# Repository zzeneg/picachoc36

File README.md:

# PicaChoc36

Low-profile split keyboard with 36 keys using XIAO controllers.

_Pica pica - european (common) magpie_

## Features

- reversible PCB
- 36 soldered ChocV1 keys
- wired/wireless versions
- top pinky key moved to side
- 3D printed case

### Wired version

- XIAO RP 2040 controller
- QMK firmware
- TRRS or USB-C connection between halves
- rotary encoder on one side
- one status LED

### Wireless version

- XIAO BLE controller
- _[TODO]_ ZMK firmware
- rotary encoder on both sides (ZMK supports only main side for now)
- on/off toggle
- battery connectors

## Photos

wired version with 3d printed case

build process

battery compartment

## Firmware

- QMK - [my fork](https://github.com/zzeneg/qmk_firmware/tree/feature/zzeneg/keyboards/picachoc36), [compiled file](https://github.com/zzeneg/qmk_firmware/releases/download/zzeneg/picachoc36_default.uf2)
- Vial - [my fork](https://github.com/zzeneg/vial-qmk/tree/feature/zzeneg/keyboards/picachoc36), [compiled file](https://github.com/zzeneg/vial-qmk/releases/download/zzeneg/picachoc36_vial.uf2)
- _[TODO]_ ZMK

## Gerber files

- [PCB](./pcb/production/pcb.zip)

## Case files (STL - 3d printed)

Updated wired cases render:

- Wired - [Left](./stl/Plate_case%20v2_left-wired.stl), [left without encoder hole](./stl/Plate_case%20v2_left-wired-no-enc.stl), [right](./stl/Plate_case%20v2_right-wired.stl), [right without encoder hole](./stl/Plate_case%20v2_right-wired-no-enc.stl)
- Wireless - with battery compartment and encoder holes - [left](./stl/Plate-wireless-left.stl), [right](./stl/Plate-wireless-right.stl)
- _[Experimental]_ [Knob](./stl/Knob.stl) for low profile rotary encoder

## Bill of materials

- PCBs
- 3D printed case
- 2 XIAO MCUs - [RP2040](https://www.seeedstudio.com/XIAO-RP2040-v1-0-p-5026.html) for wired version, [nRF52840](https://www.seeedstudio.com/Seeed-XIAO-BLE-nRF52840-p-5201.html) for wireless
- 36 Choc V1 switches
- 36 SMD SOD-123 1N4148 diodes
- 1 or 2 EC11/12 rotary encoder with knob, [low profile](https://keycapsss.com/keyboard-parts/parts/220/alps-alpine-encoder-low-profile-ec12e1220301) is recommended
- _[Wired only]_ [2x USB-C 16pin connector](https://www.aliexpress.com/item/1005003670899595.html) and TRRS jack
- _[Wired only]_ USB-C or TRRS cable
- _[Wireless only]_ 2x Li-Ion 3.7V battery (battery compartment suited for 5×12×21 size)
- _[Wireless only]_ [2x on/off toggle MSK-12C02](https://www.aliexpress.com/item/4000685483225.html)

## Build log

**TODO**

Similar to all other keyboards. Main points:

- solder diodes on **top** side
- solder jumpers - choose wired or wireless on both sides
- for wired version only - solder "no enc" jumper on the side that **does not** have encoder
- for wireless version only - solder on/off switch on **top** side
- if you want USB-C connection, I recommend to solder both TRRS and USB-C to have a backup option, better safe than sorry. Check USB-C pins with multimeter for shorts/continuity, test that encoder works (it uses connection between splits)

⚠️ It's not possible to disassemble the keyboard after soldering switches, so **before** that:

- flash your MCUs with a firmware that supports bootmagic/QK_BOOT/&reset functions
- triple check all keys with tweezers

## Development

For proper KiCad setup install my [zzkeeb](https://github.com/zzeneg/zzkeeb/blob/main/README.md#installation) library.

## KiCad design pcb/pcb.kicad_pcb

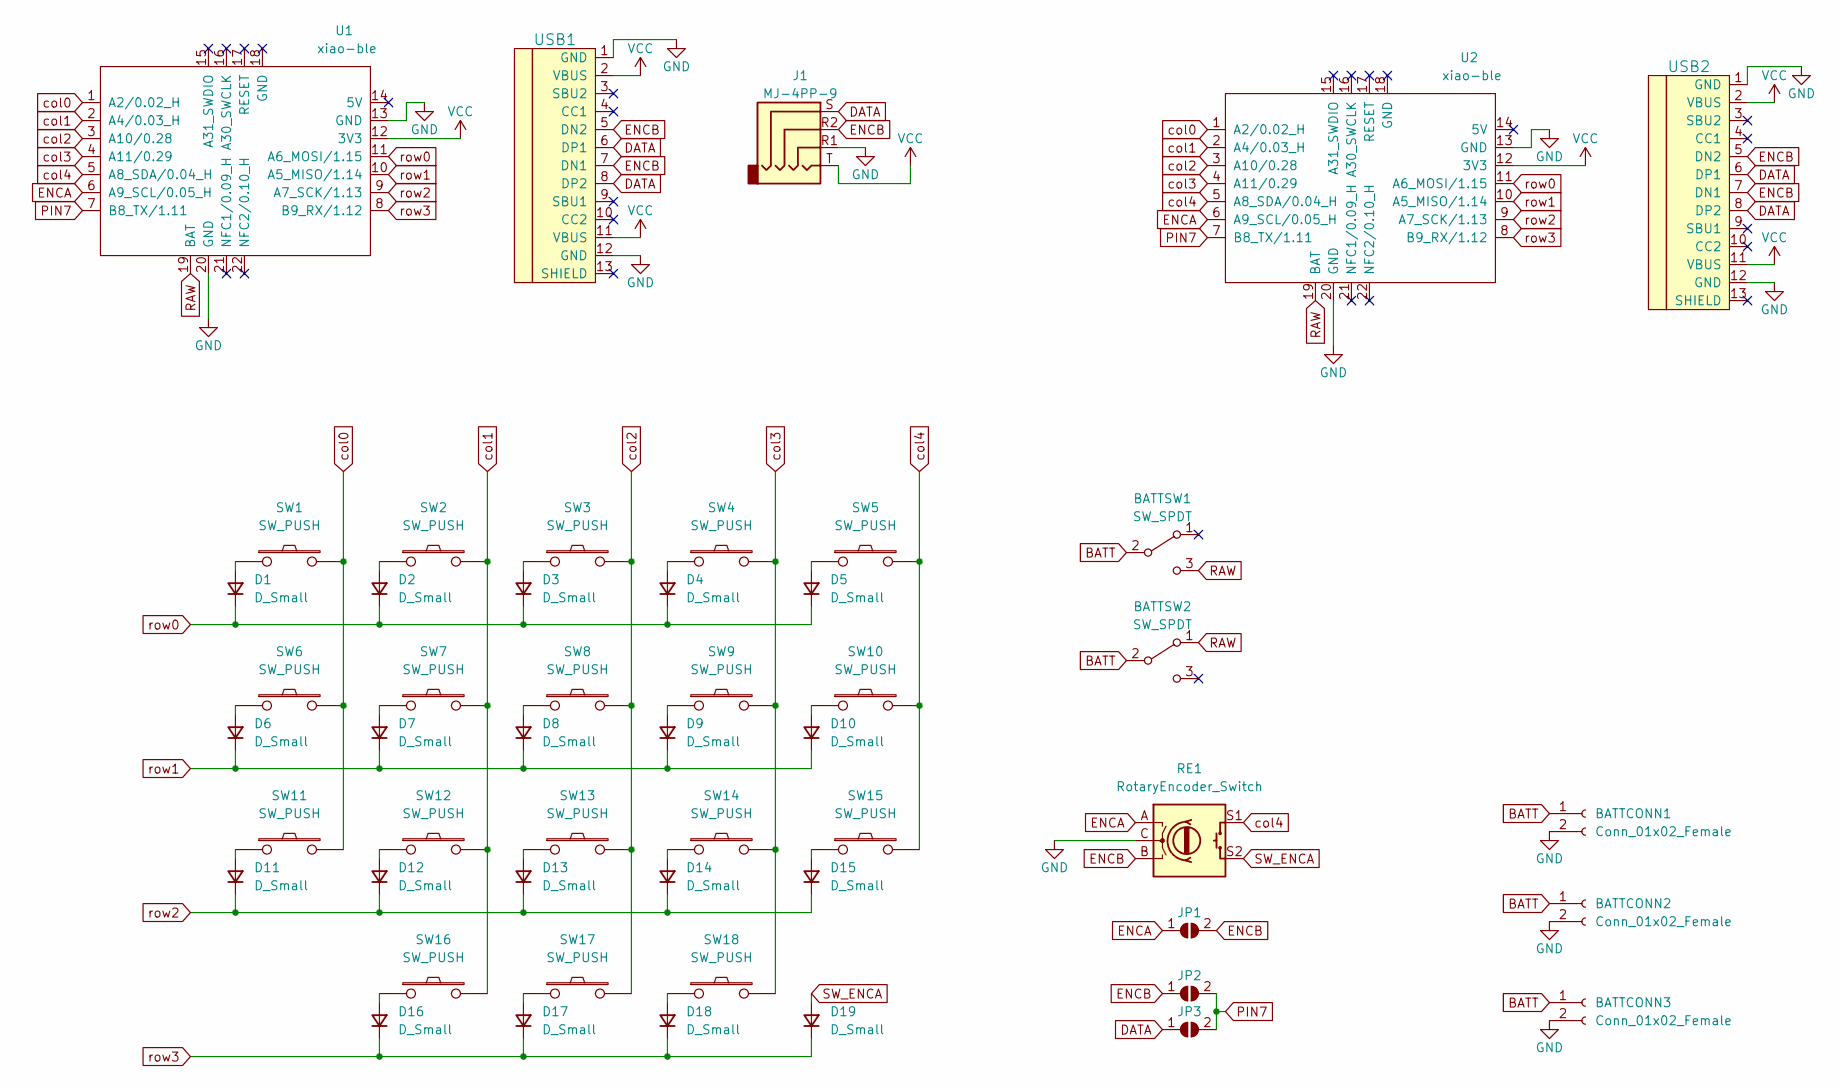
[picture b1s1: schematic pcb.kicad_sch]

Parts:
BATTCONN1, BATTCONN2, BATTCONN3: Conn_01x02_Female; Connector_JST-1x02-2.00mm
BATTSW1, BATTSW2: SW_SPDT; Switch_SPDT-PCM12
D1, D2, D3, D4, D5, D6, D7, D8, D9, D10, D11, D12, D13, D14, D15, D16, D17, D18, D19: D_Small; Diode_1N4148-SOD123-reversible
J1: MJ-4PP-9; Connector_TRRS-reversible
JP1, JP2, JP3: SolderJumper_2_Open; SolderJumper-2_P1.3mm_Open_TrianglePad1.0x1.5mm
RE1: RotaryEncoder_Switch; RotaryEncoder_EC11-reversible
SW1, SW2, SW3, SW4, SW5, SW6, SW7, SW8, SW9, SW10, SW11, SW12, SW13, SW14, SW15, SW16, SW17, SW18: SW_PUSH; Switch_ChocV1-reversible
U1, U2: xiao-ble; MCU_xiao-ble-smd
USB1, USB2: HRO-TYPE-C-31-M-12; Connector_HRO-TYPE-C-31-M-12-data

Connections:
BATT: BATTCONN1.1, BATTCONN2.1, BATTCONN3.1, BATTSW1.2 (B), BATTSW2.2 (B)
DATA: J1.S, JP3.1 (A), USB1.6 (DP1), USB1.8 (DP2), USB2.6 (DP1), USB2.8 (DP2)
ENCA: JP1.1 (A), RE1.A, U1.6 (A9_SCL/0.05_H), U2.6 (A9_SCL/0.05_H)
ENCB: J1.R2, JP1.2 (B), JP2.1 (A), RE1.B, USB1.5 (DN2), USB1.7 (DN1), USB2.5 (DN2), USB2.7 (DN1)
GND: BATTCONN1.2, BATTCONN2.2, BATTCONN3.2, J1.R1, RE1.C, U1.13 (GND), U1.20 (GND), U2.13 (GND), U2.20 (GND), USB1.1 (GND), USB1.12 (GND), USB2.1 (GND), USB2.12 (GND)
unnamed: D1.2 (A), SW1.1
unnamed: D2.2 (A), SW2.1
unnamed: D3.2 (A), SW3.1
unnamed: D4.2 (A), SW4.1
unnamed: D5.2 (A), SW5.1
unnamed: D6.2 (A), SW6.1
unnamed: D7.2 (A), SW7.1
unnamed: D8.2 (A), SW8.1
unnamed: D9.2 (A), SW9.1
unnamed: D10.2 (A), SW10.1
unnamed: D11.2 (A), SW11.1
unnamed: D12.2 (A), SW12.1
unnamed: D13.2 (A), SW13.1
unnamed: D14.2 (A), SW14.1
unnamed: D15.2 (A), SW15.1
unnamed: D16.2 (A), SW16.1
unnamed: D17.2 (A), SW17.1
unnamed: D18.2 (A), SW18.1
PIN7: JP2.2 (B), JP3.2 (B), U1.7 (B8_TX/1.11), U2.7 (B8_TX/1.11)
RAW: BATTSW1.3 (C), BATTSW2.1 (A), U1.19 (BAT), U2.19 (BAT)
SW_ENCA: D19.2 (A), RE1.S2
VCC: J1.T, U1.12 (3V3), U2.12 (3V3), USB1.2 (VBUS), USB1.11 (VBUS), USB2.2 (VBUS), USB2.11 (VBUS)
col0: SW1.2, SW6.2, SW11.2, U1.1 (A2/0.02_H), U2.1 (A2/0.02_H)
col1: SW2.2, SW7.2, SW12.2, SW16.2, U1.2 (A4/0.03_H), U2.2 (A4/0.03_H)
col2: SW3.2, SW8.2, SW13.2, SW17.2, U1.3 (A10/0.28), U2.3 (A10/0.28)
col3: SW4.2, SW9.2, SW14.2, SW18.2, U1.4 (A11/0.29), U2.4 (A11/0.29)
col4: RE1.S1, SW5.2, SW10.2, SW15.2, U1.5 (A8_SDA/0.04_H), U2.5 (A8_SDA/0.04_H)
row0: D1.1 (K), D2.1 (K), D3.1 (K), D4.1 (K), D5.1 (K), U1.11 (A6_MOSI/1.15), U2.11 (A6_MOSI/1.15)
row1: D6.1 (K), D7.1 (K), D8.1 (K), D9.1 (K), D10.1 (K), U1.10 (A5_MISO/1.14), U2.10 (A5_MISO/1.14)
row2: D11.1 (K), D12.1 (K), D13.1 (K), D14.1 (K), D15.1 (K), U1.9 (A7_SCK/1.13), U2.9 (A7_SCK/1.13)
row3: D16.1 (K), D17.1 (K), D18.1 (K), D19.1 (K), U1.8 (B9_RX/1.12), U2.8 (B9_RX/1.12)

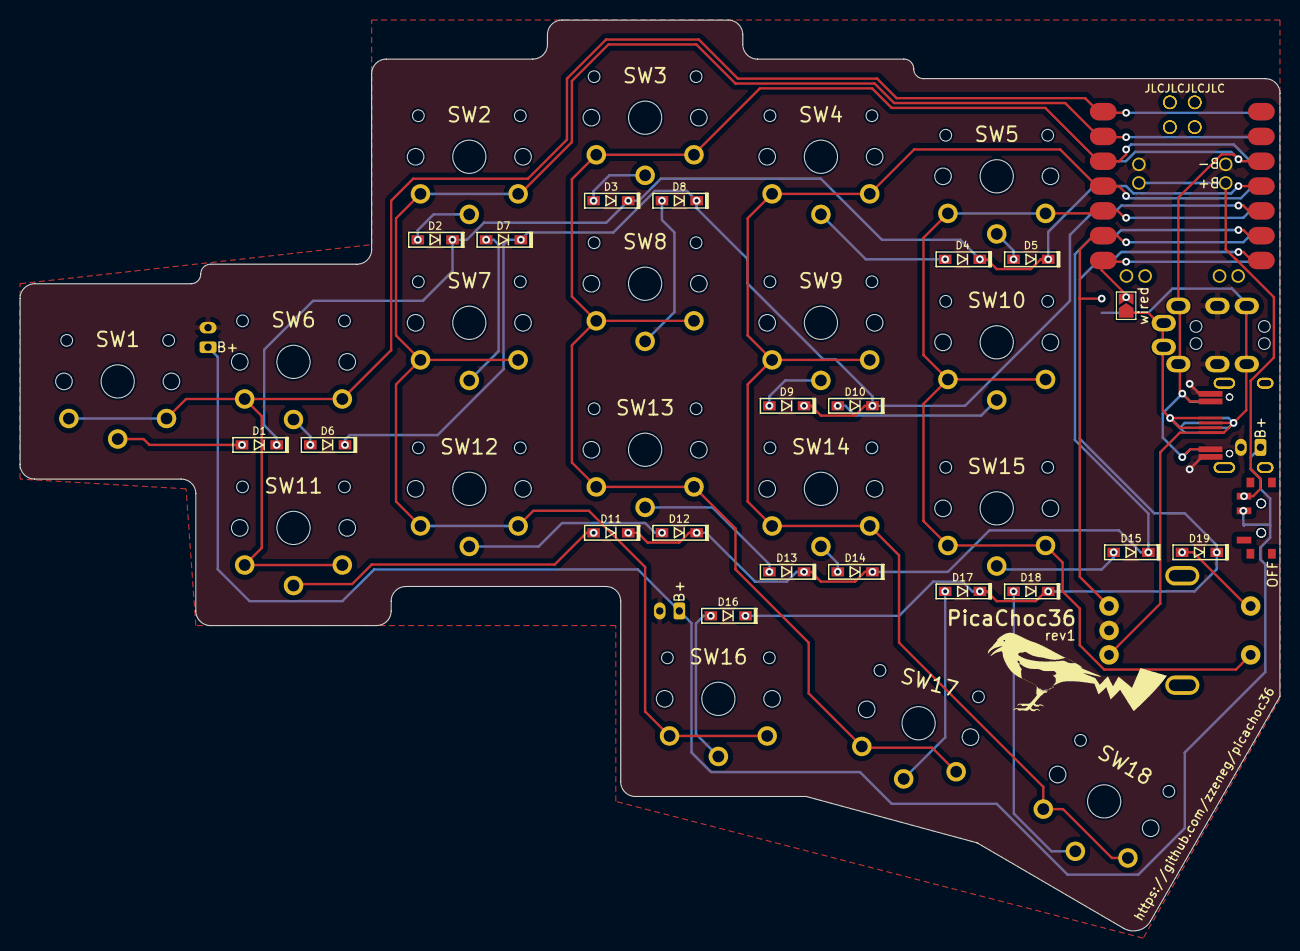
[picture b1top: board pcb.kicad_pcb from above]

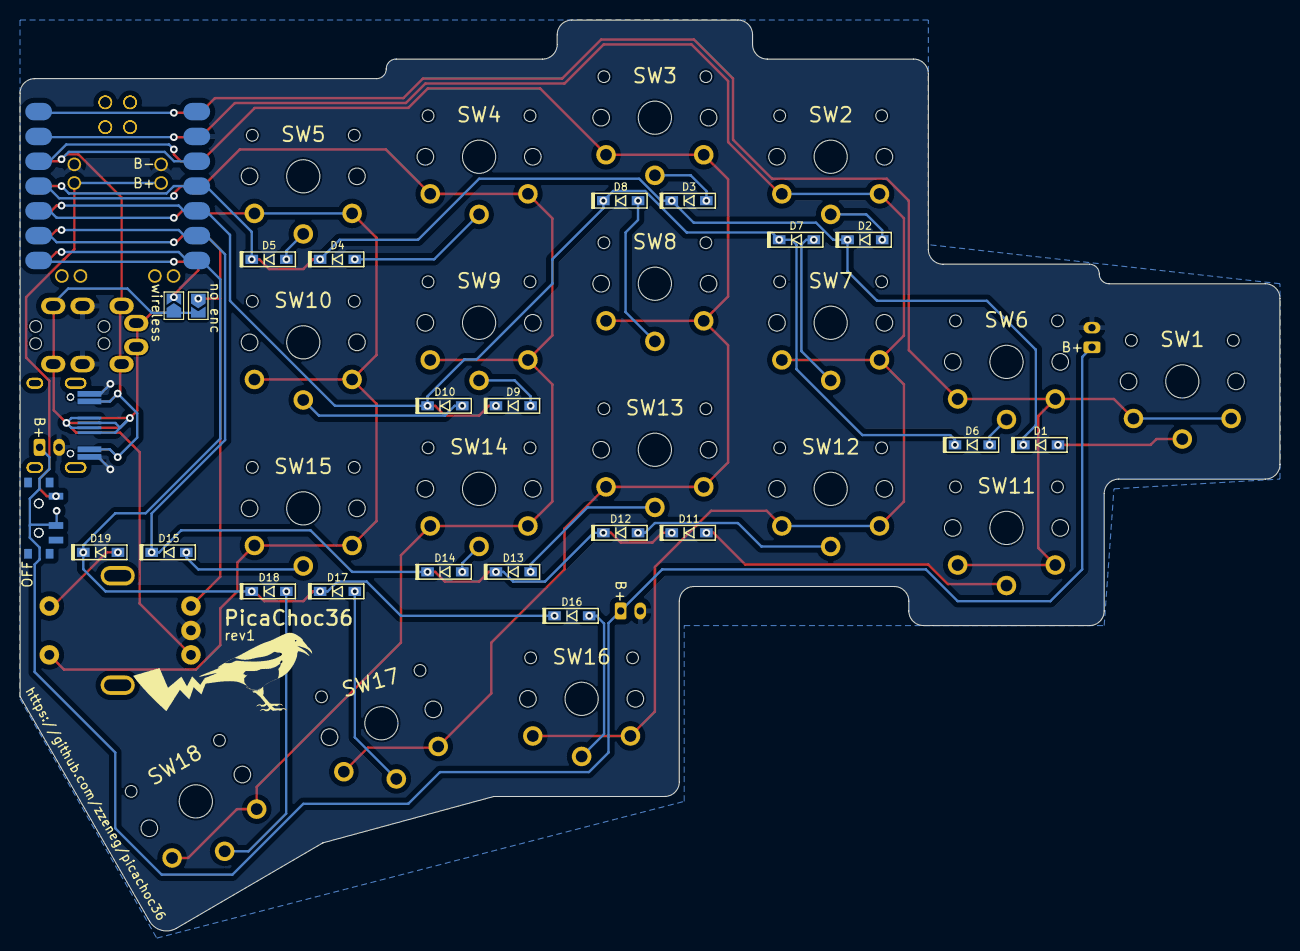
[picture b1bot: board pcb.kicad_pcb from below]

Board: 2 copper layers, 129.0 x 93.3 mm, 51 parts (5 on the bottom side), 36 nets.

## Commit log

2022-12-20 initial pcb
2022-12-20 add case
2022-12-21 improve case
2022-12-22 improve pcb
2022-12-22 fix case
2022-12-26 small pcb
2023-01-10 small fix for encoder footprint
2023-01-11 move usb-c connector a bit
2023-01-11 fix choc footprint
2023-01-11 update cases
2023-01-11 add readme
2023-01-12 Revert "fix choc footprint"
    This reverts commit fcca782c8e4dbdc4b8a54a5bbd694bc51ef22255.
2023-01-13 add knob
2023-01-14 improve vial keymap
2023-01-14 fix readme
2023-01-17 add zzkeeb
2023-01-19 new version
2023-01-23 update firmware
2023-02-18 migrate to my own library
2023-02-19 update wired cases
2023-02-19 fix images in readme
2024-04-15 restructure
